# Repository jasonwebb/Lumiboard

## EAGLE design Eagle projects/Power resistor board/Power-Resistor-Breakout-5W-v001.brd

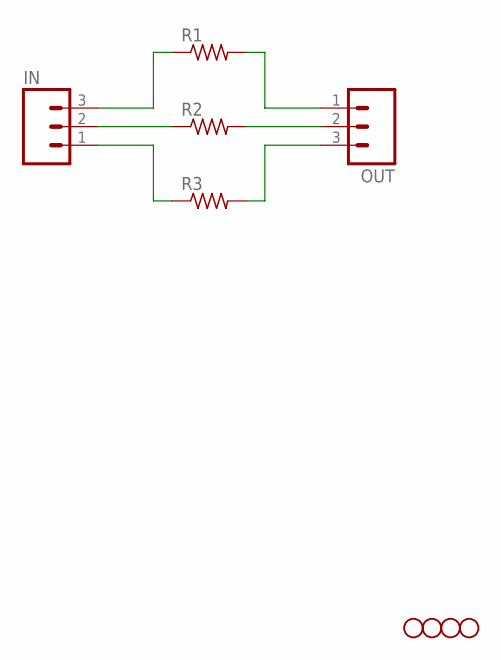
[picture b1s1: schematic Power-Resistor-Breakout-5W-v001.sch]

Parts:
IN: M03PTH; 1X03
JP1, JP2, JP3, JP4: STAND-OFF
OUT: M03PTH; 1X03
R1, R2, R3: R-US_0922/22; 0922/22

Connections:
unnamed: IN.2, R2.1
unnamed: OUT.2, R2.2
unnamed: IN.3, R1.1
unnamed: IN.1, R3.1
unnamed: OUT.3, R3.2
unnamed: OUT.1, R1.2

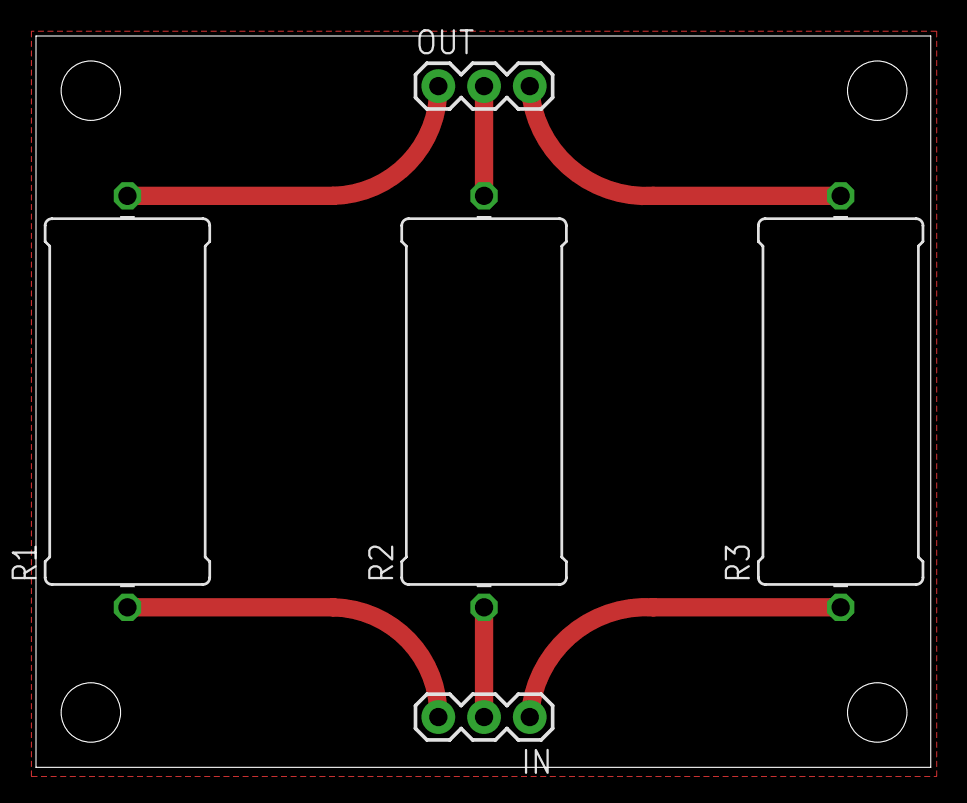
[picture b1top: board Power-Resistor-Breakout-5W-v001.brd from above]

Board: 2 copper layers, 49.7 x 40.6 mm, 9 parts (0 on the bottom side), 6 nets.

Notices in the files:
parts and their libraries:
SparkFun: Licensing: CC v3.0 Share-Alike You are welcome to use this library for commercial purposes.
